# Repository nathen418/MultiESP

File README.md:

# MultiESP

- Description: A development for simple lightweight ESP32 based systems.

# Hardware
- ESP32 (NodeMCU dev 1 package) with WiFi and Bluetooth
- NEO-M8N GPS
- DS1307 RTC and supporting battery
- 16x2 Blue Backlit LCD
- 5 color LEDS
- Piezoelectric buzzer

## How to run yourself  

- git clone <https://github.com/nathen418/MultiESP>  
- Edit the files to customize the WiFi name and password.
- Upload the appropriate sketch file to your ESP32
- Profit 💰💸

## End goal of the project

- Learn how to use the ESP32 and ESP8266 boards
- Make some cool stuff

## Credits

- [Nate](https://nathen418.com)

## Join my discord server
<https://playantares.com/discord>

## License

- MIT liscense

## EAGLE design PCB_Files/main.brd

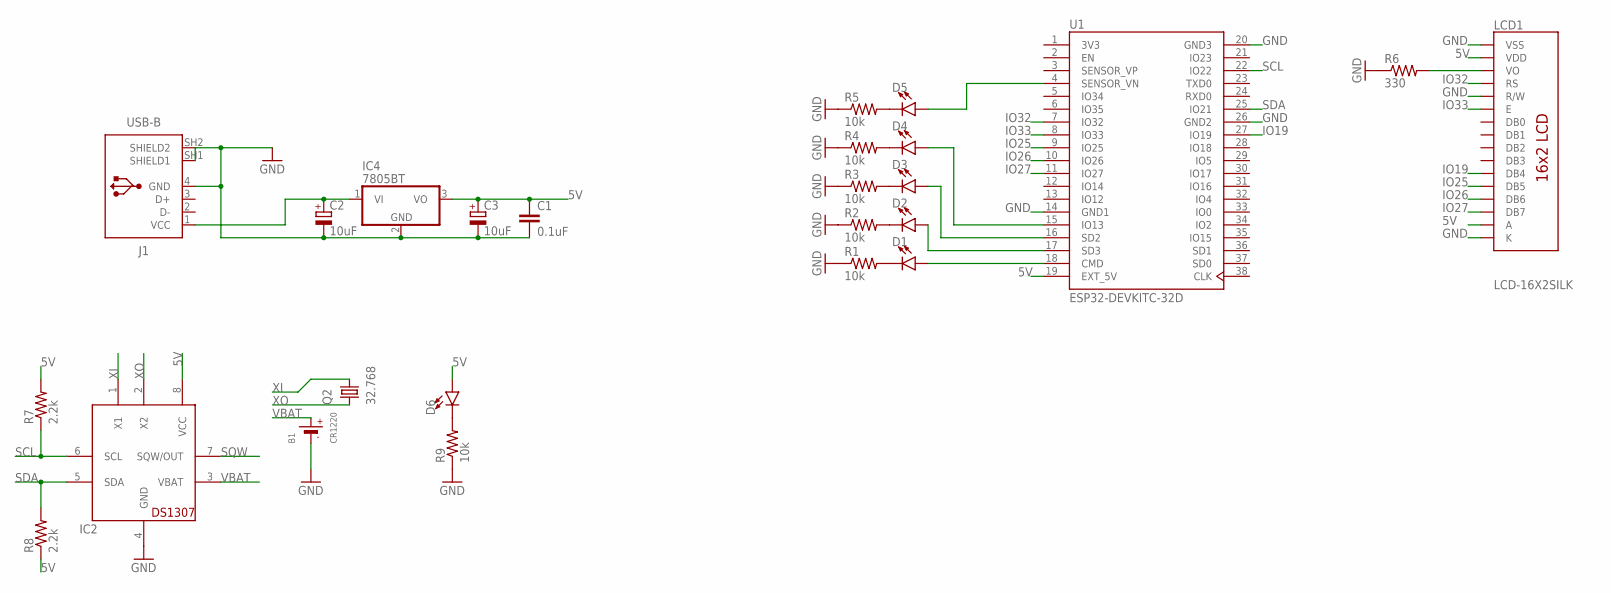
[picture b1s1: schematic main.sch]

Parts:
B1: CR1220
C1: 0.1uF; C050-024X044
C2, C3: 10uF; E2-5
D1, D2, D3, D4, D5, D6: LED5MM; LED_5MM
IC2: DS1307; DIL08
IC4: 7805BT; TO220V
J1: USB-B; 61729-1011BLF
LCD1: LCD-16X2SILK; LCD-16X2
Q2: 32.768; TC26V
R1, R2, R3, R4, R5, R9: 10k; 0207/7
R6: 330; 0207/7
R7, R8: 2.2k; 0207/7
U1: ESP32-DEVKITC-32D; MODULE_ESP32-DEVKITC-32D

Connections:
3V3: U1.1 (3V3)
5V: C1.1, C3.+, D6.A, IC2.8 (VCC), IC4.3 (VO), LCD1.2 (VDD), LCD1.15 (A), R7.2, R8.1, U1.19 (EXT_5V)
GND: B1.-, C1.2, C2.-, C3.-, IC2.4 (GND), IC4.2 (GND), J1.4 (GND), J1.SH1 (SHIELD1), J1.SH2 (SHIELD2), LCD1.1 (VSS), LCD1.5 (R/W), LCD1.16 (K), R1.1, R2.1, R3.1, R4.1, R5.1, R6.1, R9.1, U1.14 (GND1), U1.20 (GND3), U1.26 (GND2)
IO19: LCD1.11 (DB4), U1.27 (IO19)
IO25: LCD1.12 (DB5), U1.9 (IO25)
IO26: LCD1.13 (DB6), U1.10 (IO26)
IO27: LCD1.14 (DB7), U1.11 (IO27)
IO32: LCD1.4 (RS), U1.7 (IO32)
IO33: LCD1.6 (E), U1.8 (IO33)
unnamed: D6.K (C), R9.2
unnamed: D1.A, U1.18 (CMD)
unnamed: D2.A, U1.17 (SD3)
unnamed: D3.A, U1.16 (SD2)
unnamed: D4.A, U1.15 (IO13)
unnamed: D5.A, U1.4 (SENSOR_VN)
unnamed: D1.K (C), R1.2
unnamed: LCD1.3 (VO), R6.2
unnamed: D2.K (C), R2.2
unnamed: D3.K (C), R3.2
unnamed: D4.K (C), R4.2
unnamed: D5.K (C), R5.2
unnamed: C2.+, IC4.1 (VI), J1.1 (VCC)
SCL: IC2.6 (SCL), R7.1, U1.22 (IO22)
SDA: IC2.5 (SDA), R8.2, U1.25 (IO21)
SQW: IC2.7 (SQW/OUT)
VBAT: B1.+$1 (+), IC2.3 (VBAT)
XI: IC2.1 (X1), Q2.2
XO: IC2.2 (X2), Q2.1

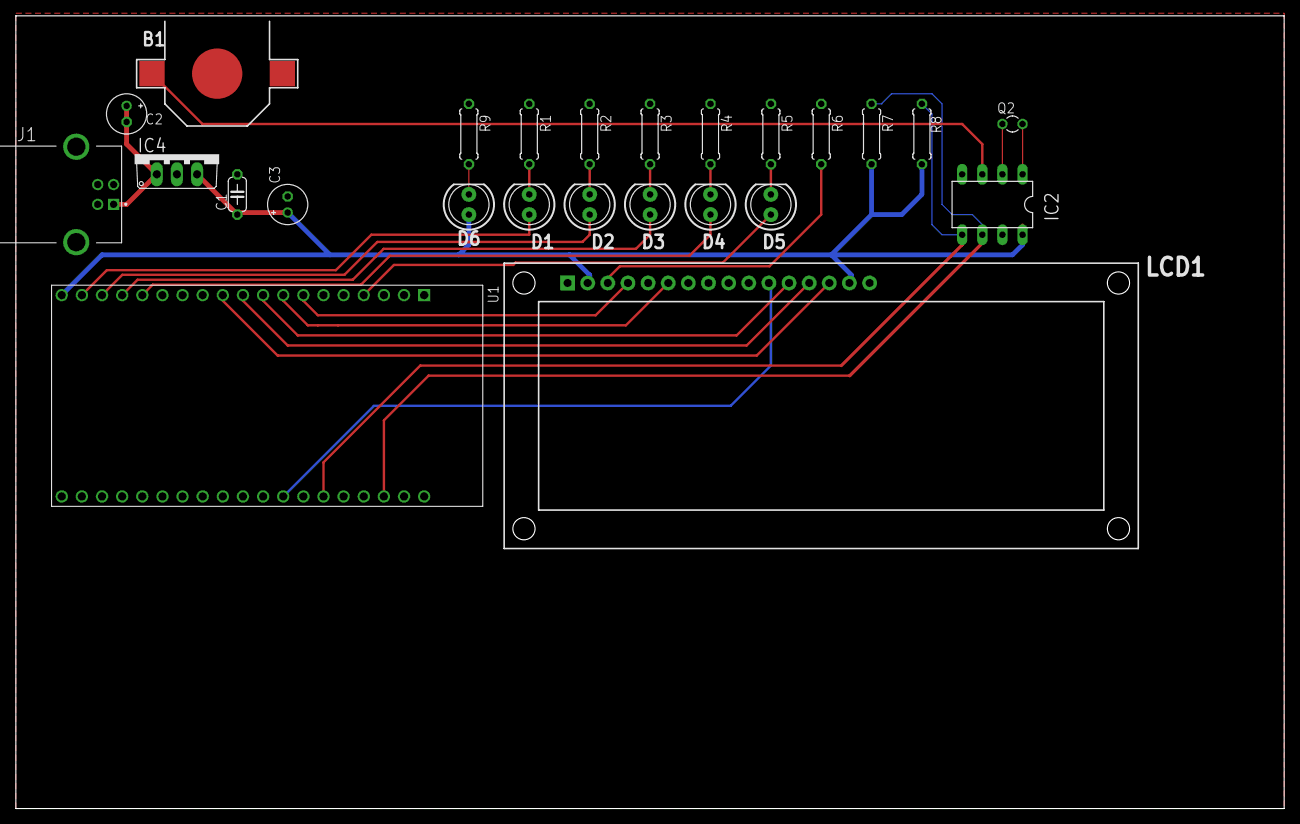
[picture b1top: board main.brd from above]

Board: 2 copper layers, 160.0 x 100.0 mm, 25 parts (0 on the bottom side), 26 nets.

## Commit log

2022-03-06 renamed
2022-03-07 Fixed some errors.
2022-03-28 add Board files and update script

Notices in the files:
parts and their libraries:
SparkFun-Displays: Licensing: Creative Commons ShareAlike 4.0 International - https://creativecommons.org/licenses/by-sa/4.0
microbuilder: This work is placed in the public domain, and may be freely used for commercial and non-commercial work with the following conditions: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
